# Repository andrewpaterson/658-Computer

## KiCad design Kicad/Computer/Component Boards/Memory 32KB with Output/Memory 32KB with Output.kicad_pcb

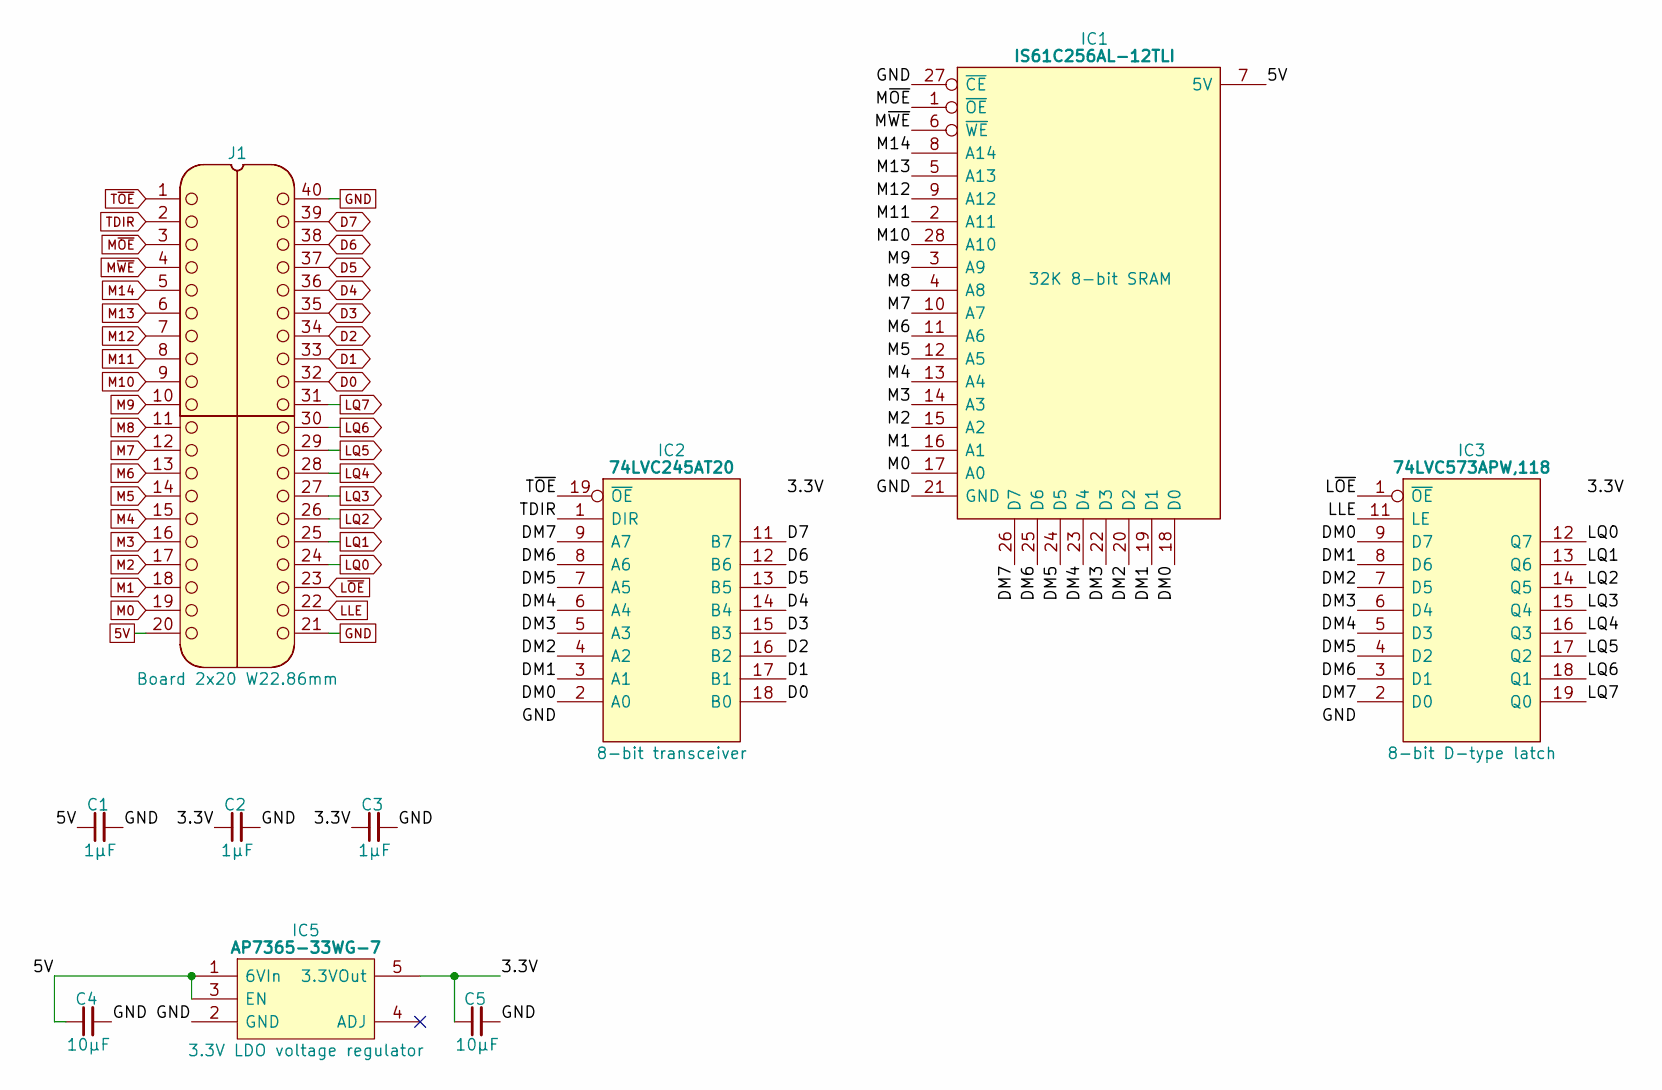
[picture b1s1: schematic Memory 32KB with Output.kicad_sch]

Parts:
C1, C2, C3: 1μF; C_0805
C4, C5: 10µF; C_0805
IC1: IS61C256AL-12TLI; SOP55P1340X120-28N; Manufacturer_Part_Number IS61C256AL-12TLI; Mouser Part Number 870-IS61C256AL-12TLI
IC2: 74LVC245AT20; SOP65P640X120-20N; Manufacturer_Part_Number 74LVC245AT20-13; Mouser Part Number 621-74LVC245AT20-13
IC3: 74LVC573APW,118; SOP65P640X110-20N; Mouser Part Number 771-74LVC573APW-T
IC5: AP7365-33WG-7; SOT95P285X130-5N; Manufacturer_Part_Number AP7365-33WG-7; Mouser Part Number 621-AP7365-33WG-7
J1: Board 2x20 W22.86mm; DIP-40_Board_W15.24mm_Alt

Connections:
5V: C1.1, C4.1, IC1.7 (5V), IC5.1 (6VIn), IC5.3 (EN), J1.20
/3.3V: C2.1, C3.1, C5.1, IC2.20 (3V), IC3.20 (3V), IC5.5 (3.3VOut)
/DM0: IC1.18 (D0), IC2.2 (A0), IC3.9 (D7)
/DM1: IC1.19 (D1), IC2.3 (A1), IC3.8 (D6)
/DM2: IC1.20 (D2), IC2.4 (A2), IC3.7 (D5)
/DM3: IC1.22 (D3), IC2.5 (A3), IC3.6 (D4)
/DM4: IC1.23 (D4), IC2.6 (A4), IC3.5 (D3)
/DM5: IC1.24 (D5), IC2.7 (A5), IC3.4 (D2)
/DM6: IC1.25 (D6), IC2.8 (A6), IC3.3 (D1)
/DM7: IC1.26 (D7), IC2.9 (A7), IC3.2 (D0)
D0: IC2.18 (B0), J1.32
D1: IC2.17 (B1), J1.33
D2: IC2.16 (B2), J1.34
D3: IC2.15 (B3), J1.35
D4: IC2.14 (B4), J1.36
D5: IC2.13 (B5), J1.37
D6: IC2.12 (B6), J1.38
D7: IC2.11 (B7), J1.39
GND: C1.2, C2.2, C3.2, C4.2, C5.2, IC1.21 (GND), IC1.27 (~CE), IC2.10 (GND), IC3.10 (GND), IC5.2 (GND), J1.21, J1.40
LLE: IC3.11 (LE), J1.22
LQ0: IC3.12 (Q7), J1.24
LQ1: IC3.13 (Q6), J1.25
LQ2: IC3.14 (Q5), J1.26
LQ3: IC3.15 (Q4), J1.27
LQ4: IC3.16 (Q3), J1.28
LQ5: IC3.17 (Q2), J1.29
LQ6: IC3.18 (Q1), J1.30
LQ7: IC3.19 (Q0), J1.31
L~OE: IC3.1 (~OE), J1.23
M0: IC1.17 (A0), J1.19
M1: IC1.16 (A1), J1.18
M2: IC1.15 (A2), J1.17
M3: IC1.14 (A3), J1.16
M4: IC1.13 (A4), J1.15
M5: IC1.12 (A5), J1.14
M6: IC1.11 (A6), J1.13
M7: IC1.10 (A7), J1.12
M8: IC1.4 (A8), J1.11
M9: IC1.3 (A9), J1.10
M10: IC1.28 (A10), J1.9
M11: IC1.2 (A11), J1.8
M12: IC1.9 (A12), J1.7
M13: IC1.5 (A13), J1.6
M14: IC1.8 (A14), J1.5
M~OE: IC1.1 (~OE), J1.3
M~WE: IC1.6 (~WE), J1.4
TDIR: IC2.1 (DIR), J1.2
T~OE: IC2.19 (~OE), J1.1

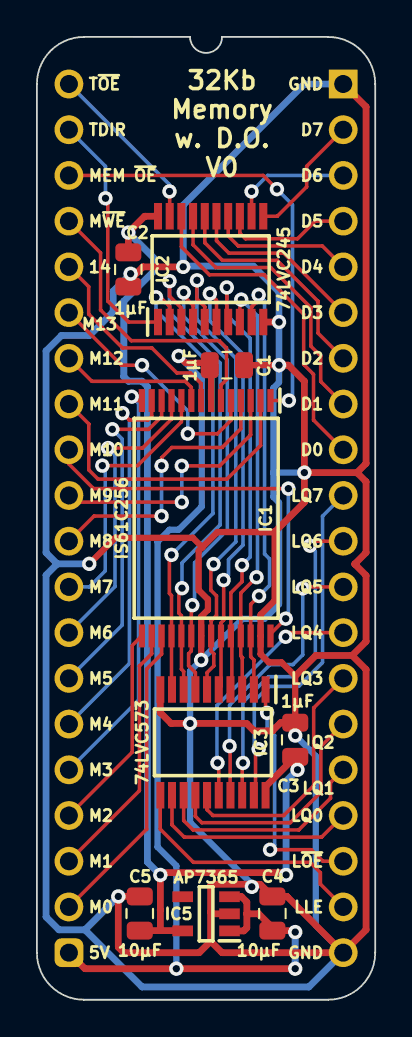
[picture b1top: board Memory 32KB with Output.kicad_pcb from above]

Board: 2 copper layers, 18.8 x 53.5 mm, 10 parts (0 on the bottom side), 48 nets.

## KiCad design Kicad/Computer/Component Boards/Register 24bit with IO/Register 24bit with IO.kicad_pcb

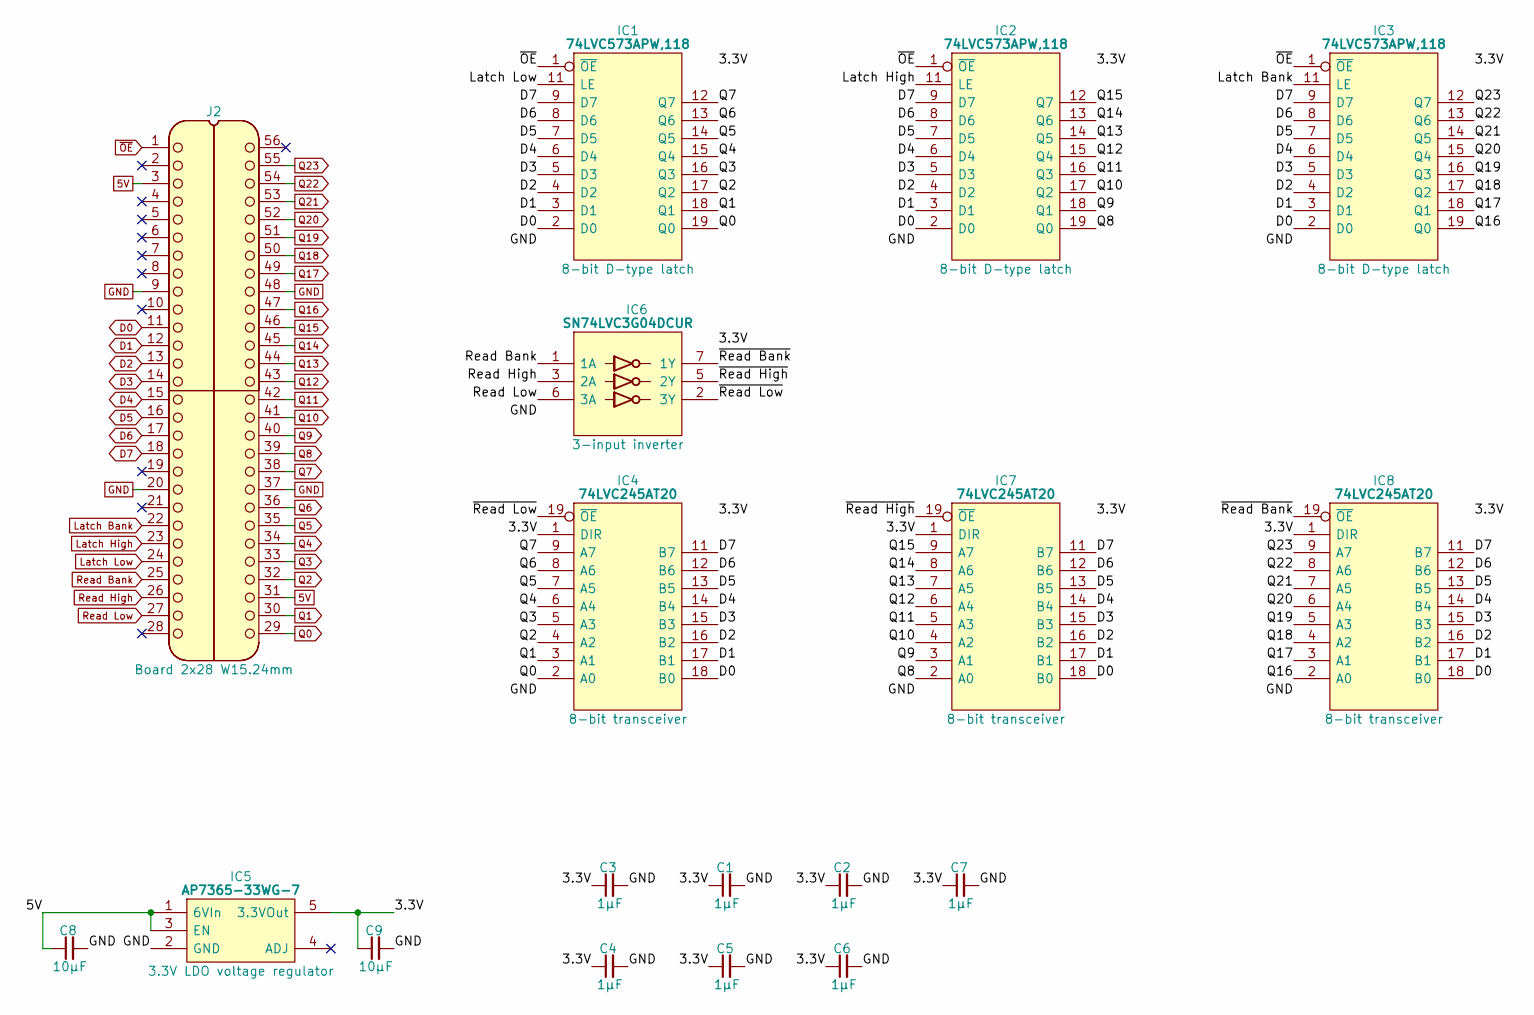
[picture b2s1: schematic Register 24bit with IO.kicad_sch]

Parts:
C1, C2, C3, C4, C5, C6, C7: 1μF; C_0805
C8, C9: 10µF; C_0805
IC1, IC2, IC3: 74LVC573APW,118; SOP65P640X110-20N; Manufacturer_Part_Number 74LVC573APW,118; Mouser Part Number 771-74LVC573APW-T
IC4, IC7, IC8: 74LVC245AT20; SOP65P640X120-20N; Manufacturer_Part_Number 74LVC245AT20-13; Mouser Part Number 621-74LVC245AT20-13
IC5: AP7365-33WG-7; SOT95P285X130-5N; Manufacturer_Part_Number AP7365-33WG-7; Mouser Part Number 621-AP7365-33WG-7
IC6: SN74LVC3G04DCUR; SOP50P310X90-8N; Manufacturer_Part_Number SN74LVC3G04DCUR; Mouser Part Number 595-SN74LVC3G04DCUR
J2: Board 2x28 W15.24mm; DIP-56_Board_W15.24mm

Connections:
5V: C8.1, IC5.1 (6VIn), IC5.3 (EN), J2.3, J2.31
/3.3V: C1.1, C2.1, C3.1, C4.1, C5.1, C6.1, C7.1, C9.1, IC1.20 (3V), IC2.20 (3V), IC3.20 (3V), IC4.1 (DIR), IC4.20 (3V), IC5.5 (3.3VOut), IC6.8 (3V), IC7.1 (DIR), IC7.20 (3V), IC8.1 (DIR), IC8.20 (3V)
/~Read Bank: IC6.7 (1Y), IC8.19 (~OE)
/~Read High: IC6.5 (2Y), IC7.19 (~OE)
/~Read Low: IC4.19 (~OE), IC6.2 (3Y)
D0: IC1.2 (D0), IC2.2 (D0), IC3.2 (D0), IC4.18 (B0), IC7.18 (B0), IC8.18 (B0), J2.11
D1: IC1.3 (D1), IC2.3 (D1), IC3.3 (D1), IC4.17 (B1), IC7.17 (B1), IC8.17 (B1), J2.12
D2: IC1.4 (D2), IC2.4 (D2), IC3.4 (D2), IC4.16 (B2), IC7.16 (B2), IC8.16 (B2), J2.13
D3: IC1.5 (D3), IC2.5 (D3), IC3.5 (D3), IC4.15 (B3), IC7.15 (B3), IC8.15 (B3), J2.14
D4: IC1.6 (D4), IC2.6 (D4), IC3.6 (D4), IC4.14 (B4), IC7.14 (B4), IC8.14 (B4), J2.15
D5: IC1.7 (D5), IC2.7 (D5), IC3.7 (D5), IC4.13 (B5), IC7.13 (B5), IC8.13 (B5), J2.16
D6: IC1.8 (D6), IC2.8 (D6), IC3.8 (D6), IC4.12 (B6), IC7.12 (B6), IC8.12 (B6), J2.17
D7: IC1.9 (D7), IC2.9 (D7), IC3.9 (D7), IC4.11 (B7), IC7.11 (B7), IC8.11 (B7), J2.18
GND: C1.2, C2.2, C3.2, C4.2, C5.2, C6.2, C7.2, C8.2, C9.2, IC1.10 (GND), IC2.10 (GND), IC3.10 (GND), IC4.10 (GND), IC5.2 (GND), IC6.4 (GND), IC7.10 (GND), IC8.10 (GND), J2.9, J2.20, J2.37, J2.48
Latch Bank: IC3.11 (LE), J2.22
Latch High: IC2.11 (LE), J2.23
Latch Low: IC1.11 (LE), J2.24
Q0: IC1.19 (Q0), IC4.2 (A0), J2.29
Q1: IC1.18 (Q1), IC4.3 (A1), J2.30
Q2: IC1.17 (Q2), IC4.4 (A2), J2.32
Q3: IC1.16 (Q3), IC4.5 (A3), J2.33
Q4: IC1.15 (Q4), IC4.6 (A4), J2.34
Q5: IC1.14 (Q5), IC4.7 (A5), J2.35
Q6: IC1.13 (Q6), IC4.8 (A6), J2.36
Q7: IC1.12 (Q7), IC4.9 (A7), J2.38
Q8: IC2.19 (Q0), IC7.2 (A0), J2.39
Q9: IC2.18 (Q1), IC7.3 (A1), J2.40
Q10: IC2.17 (Q2), IC7.4 (A2), J2.41
Q11: IC2.16 (Q3), IC7.5 (A3), J2.42
Q12: IC2.15 (Q4), IC7.6 (A4), J2.43
Q13: IC2.14 (Q5), IC7.7 (A5), J2.44
Q14: IC2.13 (Q6), IC7.8 (A6), J2.45
Q15: IC2.12 (Q7), IC7.9 (A7), J2.46
Q16: IC3.19 (Q0), IC8.2 (A0), J2.47
Q17: IC3.18 (Q1), IC8.3 (A1), J2.49
Q18: IC3.17 (Q2), IC8.4 (A2), J2.50
Q19: IC3.16 (Q3), IC8.5 (A3), J2.51
Q20: IC3.15 (Q4), IC8.6 (A4), J2.52
Q21: IC3.14 (Q5), IC8.7 (A5), J2.53
Q22: IC3.13 (Q6), IC8.8 (A6), J2.54
Q23: IC3.12 (Q7), IC8.9 (A7), J2.55
Read Bank: IC6.1 (1A), J2.25
Read High: IC6.3 (2A), J2.26
Read Low: IC6.6 (3A), J2.27
~OE: IC1.1 (~OE), IC2.1 (~OE), IC3.1 (~OE), J2.1

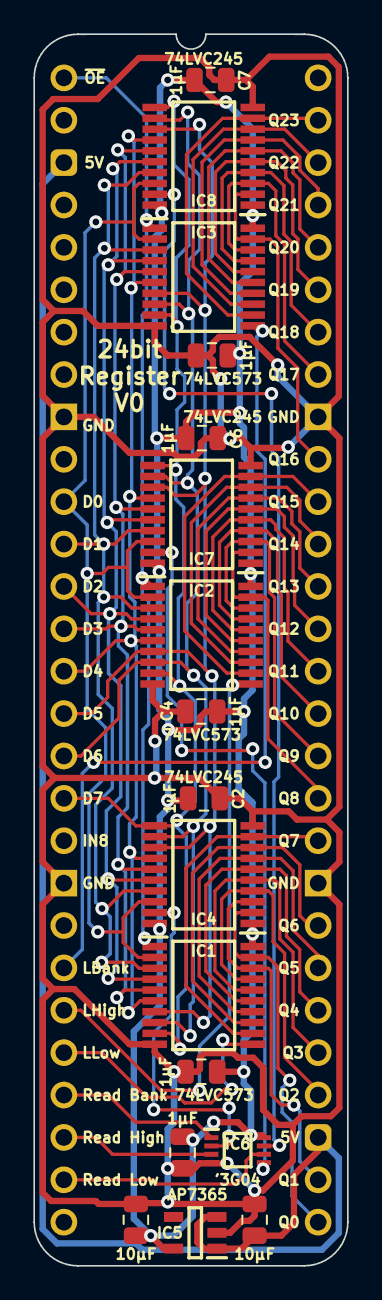
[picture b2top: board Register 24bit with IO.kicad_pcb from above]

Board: 2 copper layers, 18.8 x 73.8 mm, 18 parts (0 on the bottom side), 45 nets.

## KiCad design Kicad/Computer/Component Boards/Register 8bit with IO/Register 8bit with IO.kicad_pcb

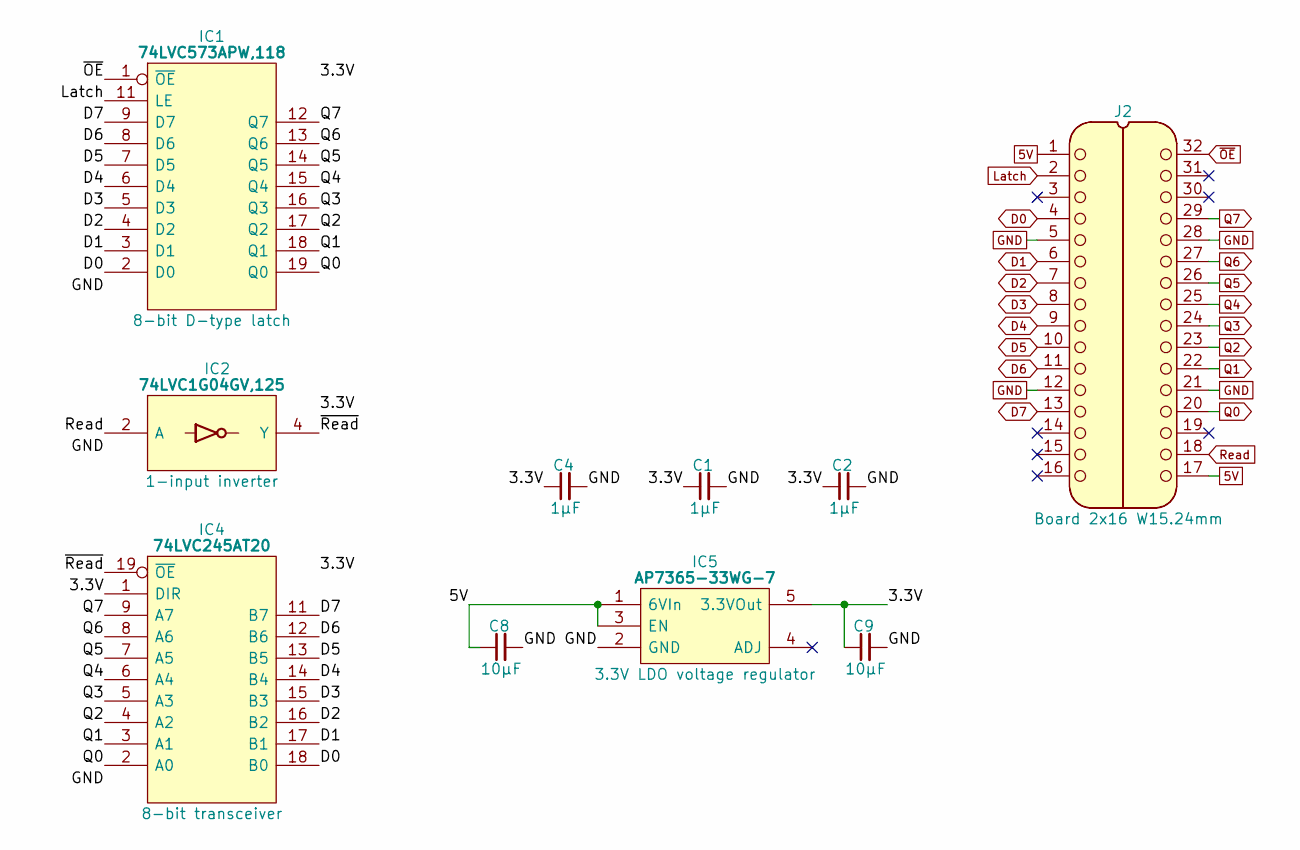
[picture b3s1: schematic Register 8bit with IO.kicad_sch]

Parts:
C1, C2, C4: 1μF; C_0805
C8, C9: 10µF; C_0805
IC1: 74LVC573APW,118; SOP65P640X110-20N; Manufacturer_Part_Number 74LVC573APW,118; Mouser Part Number 771-74LVC573APW-T
IC2: 74LVC1G04GV,125; SOT95P275X110-5N; Manufacturer_Part_Number 74LVC1G04GV,125; Mouser Part Number 771-74LVC1G04GV
IC4: 74LVC245AT20; SOP65P640X120-20N; Manufacturer_Part_Number 74LVC245AT20-13; Mouser Part Number 621-74LVC245AT20-13
IC5: AP7365-33WG-7; SOT95P285X130-5N; Manufacturer_Part_Number AP7365-33WG-7; Mouser Part Number 621-AP7365-33WG-7
J2: Board 2x16 W15.24mm; DIP-32_Board_W15.24mm

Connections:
5V: C8.1, IC5.1 (6VIn), IC5.3 (EN), J2.1, J2.17
/3.3V: C1.1, C2.1, C4.1, C9.1, IC1.20 (3V), IC2.5 (3V), IC4.1 (DIR), IC4.20 (3V), IC5.5 (3.3VOut)
/~Read: IC2.4 (Y), IC4.19 (~OE)
D0: IC1.2 (D0), IC4.18 (B0), J2.4
D1: IC1.3 (D1), IC4.17 (B1), J2.6
D2: IC1.4 (D2), IC4.16 (B2), J2.7
D3: IC1.5 (D3), IC4.15 (B3), J2.8
D4: IC1.6 (D4), IC4.14 (B4), J2.9
D5: IC1.7 (D5), IC4.13 (B5), J2.10
D6: IC1.8 (D6), IC4.12 (B6), J2.11
D7: IC1.9 (D7), IC4.11 (B7), J2.13
GND: C1.2, C2.2, C4.2, C8.2, C9.2, IC1.10 (GND), IC2.3 (GND), IC4.10 (GND), IC5.2 (GND), J2.5, J2.12, J2.21, J2.28
Latch: IC1.11 (LE), J2.2
Q0: IC1.19 (Q0), IC4.2 (A0), J2.20
Q1: IC1.18 (Q1), IC4.3 (A1), J2.22
Q2: IC1.17 (Q2), IC4.4 (A2), J2.23
Q3: IC1.16 (Q3), IC4.5 (A3), J2.24
Q4: IC1.15 (Q4), IC4.6 (A4), J2.25
Q5: IC1.14 (Q5), IC4.7 (A5), J2.26
Q6: IC1.13 (Q6), IC4.8 (A6), J2.27
Q7: IC1.12 (Q7), IC4.9 (A7), J2.29
Read: IC2.2 (A), J2.18
~OE: IC1.1 (~OE), J2.32

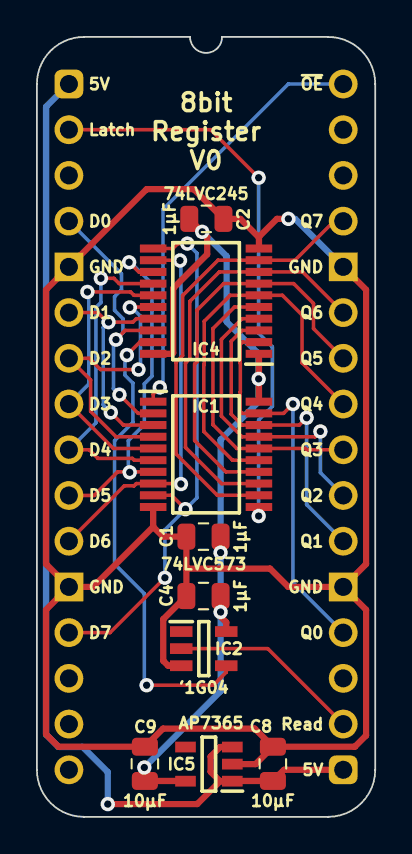
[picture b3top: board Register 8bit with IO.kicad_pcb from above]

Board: 2 copper layers, 18.8 x 43.3 mm, 10 parts (0 on the bottom side), 23 nets.

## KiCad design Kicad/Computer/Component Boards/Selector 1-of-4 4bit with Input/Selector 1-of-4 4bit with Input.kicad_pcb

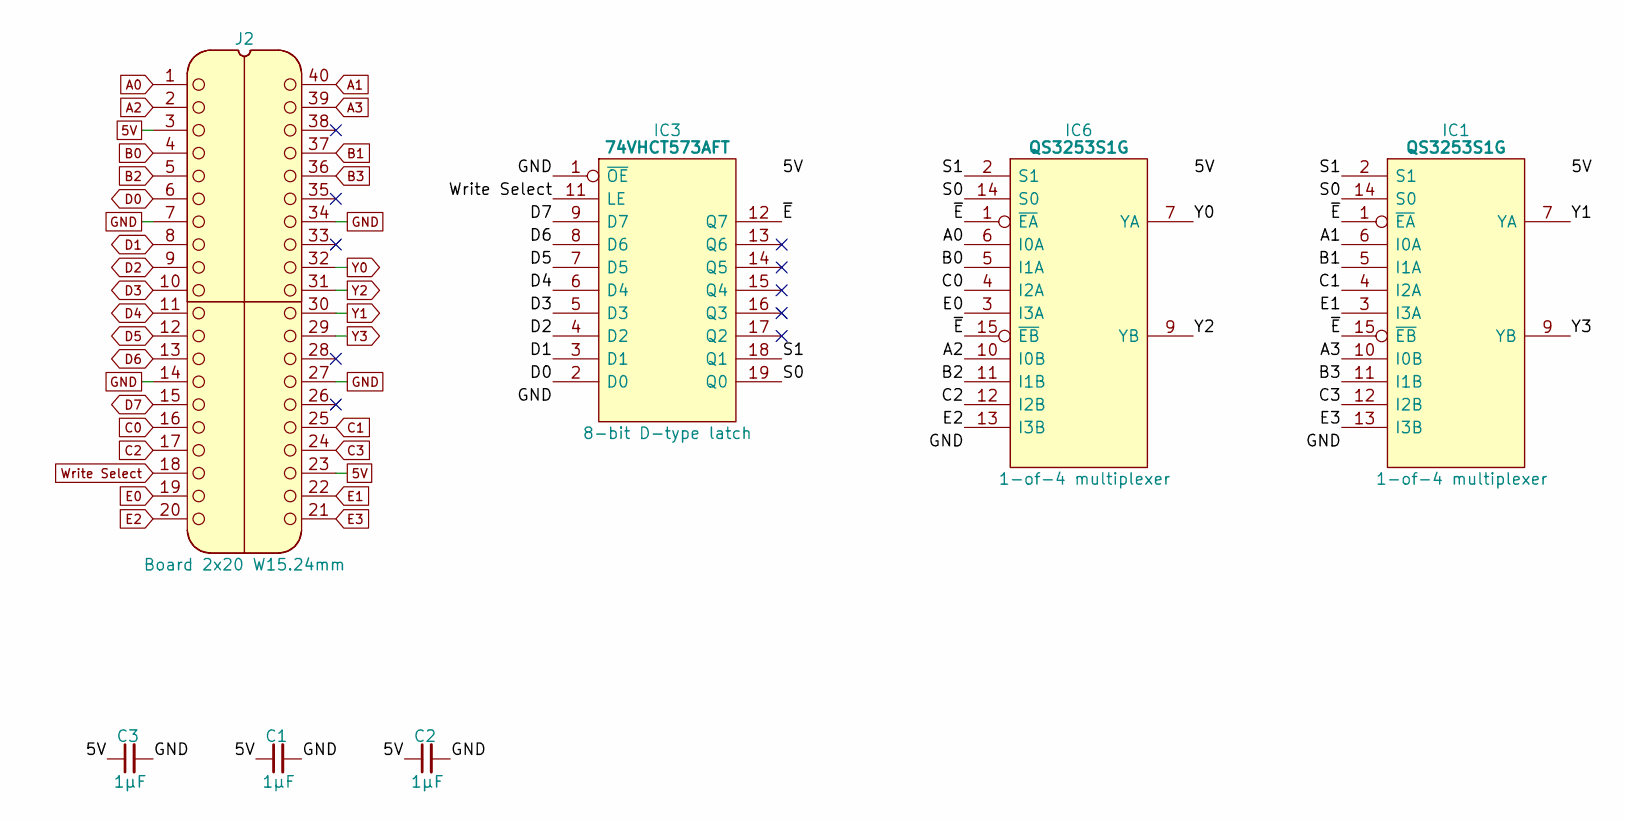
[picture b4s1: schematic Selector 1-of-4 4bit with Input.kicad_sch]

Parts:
C1, C2, C3: 1μF; C_0805
IC1, IC6: QS3253S1G; SOIC127P602X173-16N; Manufacturer_Part_Number QS3253S1G
IC3: 74VHCT573AFT; SOP65P640X120-20N; Manufacturer_Part_Number 74VHCT573AFT; Mouser Part Number N/A
J2: Board 2x20 W15.24mm; DIP-40_Board_W15.24mm

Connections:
5V: C1.1, C2.1, C3.1, IC1.16 (5V), IC3.20 (5V), IC6.16 (5V), J2.3, J2.23
/S0: IC1.14 (S0), IC3.19 (Q0), IC6.14 (S0)
/S1: IC1.2 (S1), IC3.18 (Q1), IC6.2 (S1)
/~E: IC1.1 (~EA), IC1.15 (~EB), IC3.12 (Q7), IC6.1 (~EA), IC6.15 (~EB)
A0: IC6.6 (I0A), J2.1
A1: IC1.6 (I0A), J2.40
A2: IC6.10 (I0B), J2.2
A3: IC1.10 (I0B), J2.39
B0: IC6.5 (I1A), J2.4
B1: IC1.5 (I1A), J2.37
B2: IC6.11 (I1B), J2.5
B3: IC1.11 (I1B), J2.36
C0: IC6.4 (I2A), J2.16
C1: IC1.4 (I2A), J2.25
C2: IC6.12 (I2B), J2.17
C3: IC1.12 (I2B), J2.24
D0: IC3.2 (D0), J2.6
D1: IC3.3 (D1), J2.8
D2: IC3.4 (D2), J2.9
D3: IC3.5 (D3), J2.10
D4: IC3.6 (D4), J2.11
D5: IC3.7 (D5), J2.12
D6: IC3.8 (D6), J2.13
D7: IC3.9 (D7), J2.15
E0: IC6.3 (I3A), J2.19
E1: IC1.3 (I3A), J2.22
E2: IC6.13 (I3B), J2.20
E3: IC1.13 (I3B), J2.21
GND: C1.2, C2.2, C3.2, IC1.8 (GND), IC3.1 (~OE), IC3.10 (GND), IC6.8 (GND), J2.7, J2.14, J2.27, J2.34
Write Select: IC3.11 (LE), J2.18
Y0: IC6.7 (YA), J2.32
Y1: IC1.7 (YA), J2.30
Y2: IC6.9 (YB), J2.31
Y3: IC1.9 (YB), J2.29

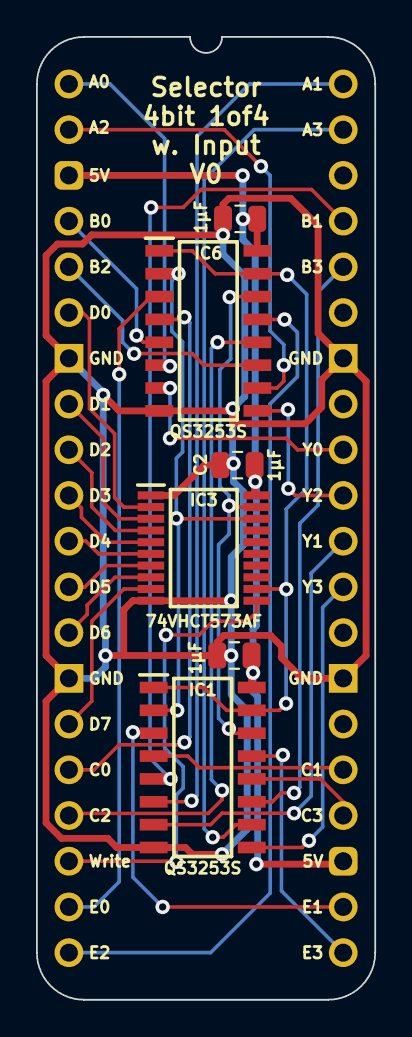
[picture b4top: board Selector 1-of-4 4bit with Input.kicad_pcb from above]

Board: 2 copper layers, 18.8 x 53.5 mm, 7 parts (0 on the bottom side), 34 nets.

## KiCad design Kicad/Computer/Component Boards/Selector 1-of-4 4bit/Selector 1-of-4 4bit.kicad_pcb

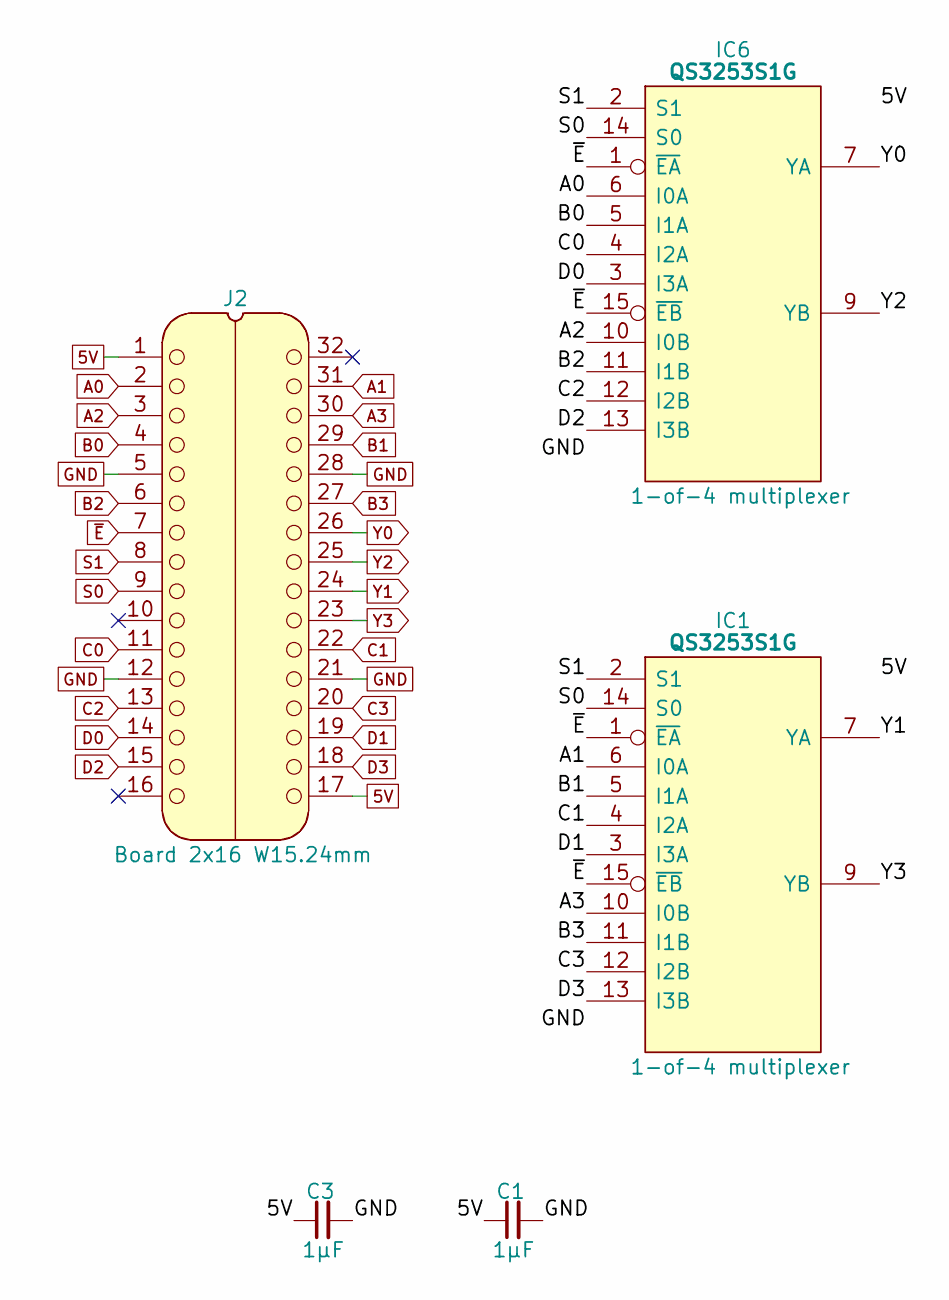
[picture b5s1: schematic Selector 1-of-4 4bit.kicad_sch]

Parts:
C1, C3: 1μF; C_0805
IC1, IC6: QS3253S1G; SOIC127P602X173-16N; Manufacturer_Part_Number QS3253S1G
J2: Board 2x16 W15.24mm; DIP-32_Board_W15.24mm

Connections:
5V: C1.1, C3.1, IC1.16 (5V), IC6.16 (5V), J2.1, J2.17
A0: IC6.6 (I0A), J2.2
A1: IC1.6 (I0A), J2.31
A2: IC6.10 (I0B), J2.3
A3: IC1.10 (I0B), J2.30
B0: IC6.5 (I1A), J2.4
B1: IC1.5 (I1A), J2.29
B2: IC6.11 (I1B), J2.6
B3: IC1.11 (I1B), J2.27
C0: IC6.4 (I2A), J2.11
C1: IC1.4 (I2A), J2.22
C2: IC6.12 (I2B), J2.13
C3: IC1.12 (I2B), J2.20
D0: IC6.3 (I3A), J2.14
D1: IC1.3 (I3A), J2.19
D2: IC6.13 (I3B), J2.15
D3: IC1.13 (I3B), J2.18
GND: C1.2, C3.2, IC1.8 (GND), IC6.8 (GND), J2.5, J2.12, J2.21, J2.28
S0: IC1.14 (S0), IC6.14 (S0), J2.9
S1: IC1.2 (S1), IC6.2 (S1), J2.8
Y0: IC6.7 (YA), J2.26
Y1: IC1.7 (YA), J2.24
Y2: IC6.9 (YB), J2.25
Y3: IC1.9 (YB), J2.23
~E: IC1.1 (~EA), IC1.15 (~EB), IC6.1 (~EA), IC6.15 (~EB), J2.7

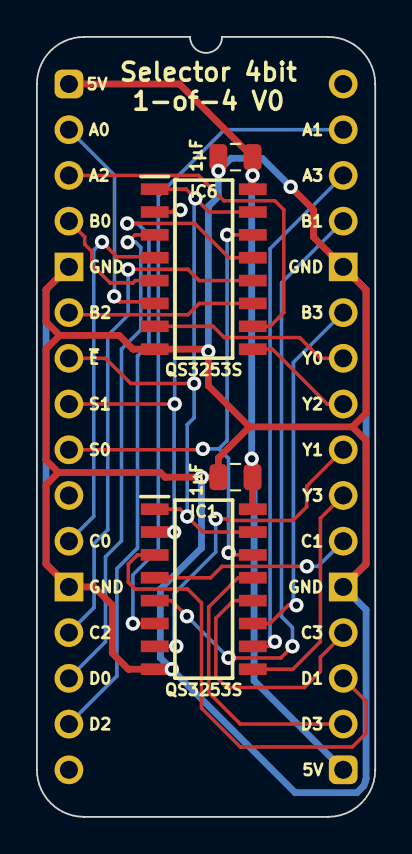
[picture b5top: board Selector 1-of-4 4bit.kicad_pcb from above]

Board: 2 copper layers, 18.8 x 43.3 mm, 5 parts (0 on the bottom side), 25 nets.

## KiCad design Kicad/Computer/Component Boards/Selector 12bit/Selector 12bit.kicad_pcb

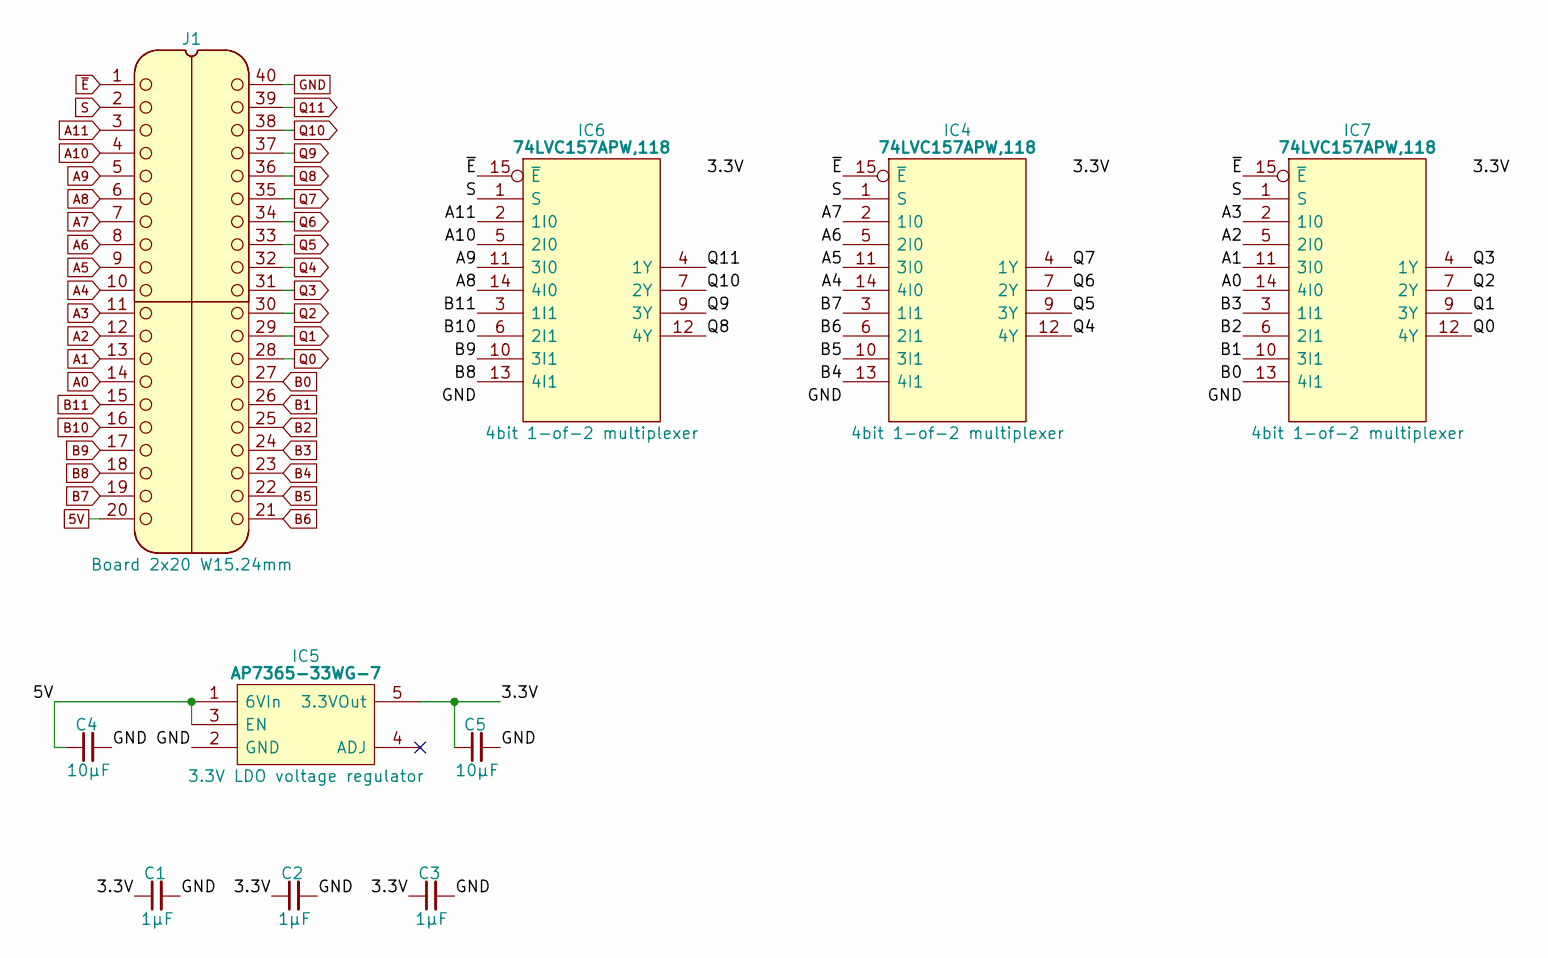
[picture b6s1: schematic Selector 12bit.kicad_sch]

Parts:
C1, C2, C3: 1μF; C_0805
C4, C5: 10µF; C_0805
IC4, IC6, IC7: 74LVC157APW,118; SOP65P640X110-16N; Mouser Part Number 771-74LVC157APW-T
IC5: AP7365-33WG-7; SOT95P285X130-5N; Manufacturer_Part_Number AP7365-33WG-7; Mouser Part Number 621-AP7365-33WG-7
J1: Board 2x20 W15.24mm; DIP-40_Board_W15.24mm_Alt

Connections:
5V: C4.1, IC5.1 (6VIn), IC5.3 (EN), J1.20
/3.3V: C1.1, C2.1, C3.1, C5.1, IC4.16 (3V), IC5.5 (3.3VOut), IC6.16 (3V), IC7.16 (3V)
A0: IC7.14 (4I0), J1.14
A1: IC7.11 (3I0), J1.13
A2: IC7.5 (2I0), J1.12
A3: IC7.2 (1I0), J1.11
A4: IC4.14 (4I0), J1.10
A5: IC4.11 (3I0), J1.9
A6: IC4.5 (2I0), J1.8
A7: IC4.2 (1I0), J1.7
A8: IC6.14 (4I0), J1.6
A9: IC6.11 (3I0), J1.5
A10: IC6.5 (2I0), J1.4
A11: IC6.2 (1I0), J1.3
B0: IC7.13 (4I1), J1.27
B1: IC7.10 (3I1), J1.26
B2: IC7.6 (2I1), J1.25
B3: IC7.3 (1I1), J1.24
B4: IC4.13 (4I1), J1.23
B5: IC4.10 (3I1), J1.22
B6: IC4.6 (2I1), J1.21
B7: IC4.3 (1I1), J1.19
B8: IC6.13 (4I1), J1.18
B9: IC6.10 (3I1), J1.17
B10: IC6.6 (2I1), J1.16
B11: IC6.3 (1I1), J1.15
GND: C1.2, C2.2, C3.2, C4.2, C5.2, IC4.8 (GND), IC5.2 (GND), IC6.8 (GND), IC7.8 (GND), J1.40
Q0: IC7.12 (4Y), J1.28
Q1: IC7.9 (3Y), J1.29
Q2: IC7.7 (2Y), J1.30
Q3: IC7.4 (1Y), J1.31
Q4: IC4.12 (4Y), J1.32
Q5: IC4.9 (3Y), J1.33
Q6: IC4.7 (2Y), J1.34
Q7: IC4.4 (1Y), J1.35
Q8: IC6.12 (4Y), J1.36
Q9: IC6.9 (3Y), J1.37
Q10: IC6.7 (2Y), J1.38
Q11: IC6.4 (1Y), J1.39
S: IC4.1 (S), IC6.1 (S), IC7.1 (S), J1.2
~E: IC4.15 (~E), IC6.15 (~E), IC7.15 (~E), J1.1

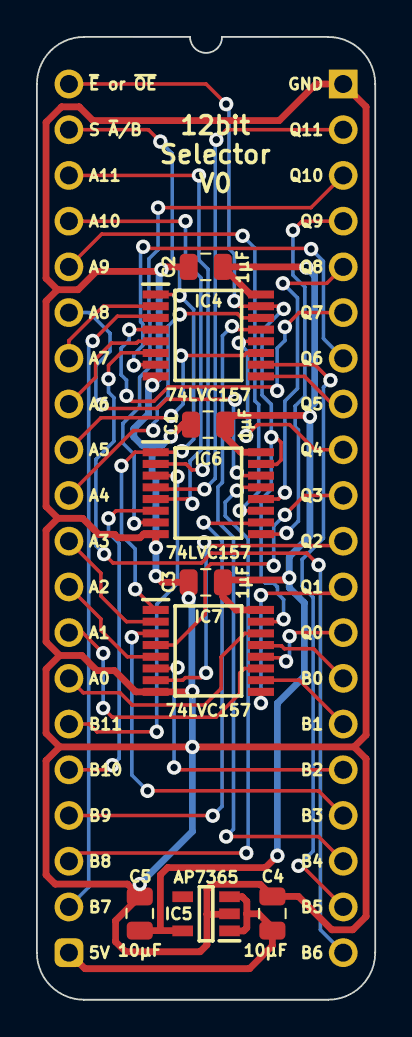
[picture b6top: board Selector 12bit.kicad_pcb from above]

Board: 2 copper layers, 18.8 x 53.5 mm, 10 parts (0 on the bottom side), 41 nets.

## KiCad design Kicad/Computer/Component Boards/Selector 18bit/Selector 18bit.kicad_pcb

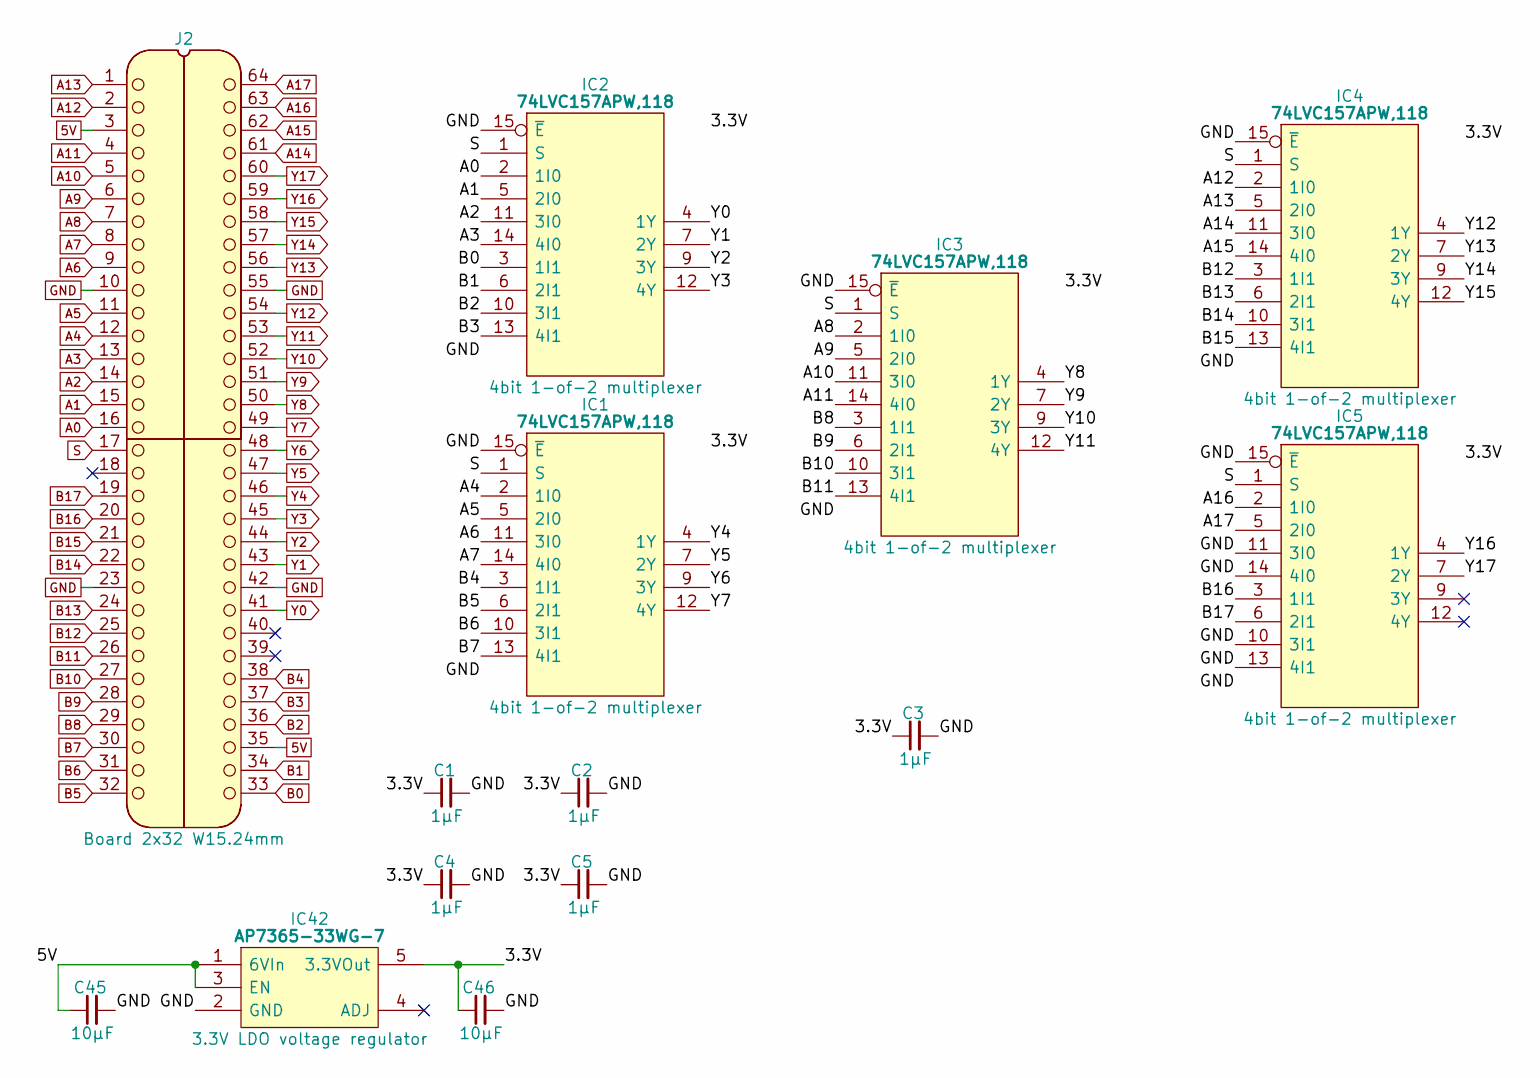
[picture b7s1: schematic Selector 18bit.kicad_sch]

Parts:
C1, C2, C3, C4, C5: 1μF; C_0805
C45, C46: 10μF; C_0805
IC1, IC2, IC3, IC4, IC5: 74LVC157APW,118; SOP65P640X110-16N; Mouser Part Number 771-74LVC157APW-T
IC42: AP7365-33WG-7; SOT95P285X130-5N; Manufacturer_Part_Number AP7365-33WG-7; Mouser Part Number 621-AP7365-33WG-7
J2: Board 2x32 W15.24mm; DIP-64_Board_W15.24mm

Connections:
5V: C45.1, IC42.1 (6VIn), IC42.3 (EN), J2.3, J2.35
/3.3V: C1.1, C2.1, C3.1, C4.1, C5.1, C46.1, IC1.16 (3V), IC2.16 (3V), IC3.16 (3V), IC4.16 (3V), IC5.16 (3V), IC42.5 (3.3VOut)
A0: IC2.2 (1I0), J2.16
A1: IC2.5 (2I0), J2.15
A2: IC2.11 (3I0), J2.14
A3: IC2.14 (4I0), J2.13
A4: IC1.2 (1I0), J2.12
A5: IC1.5 (2I0), J2.11
A6: IC1.11 (3I0), J2.9
A7: IC1.14 (4I0), J2.8
A8: IC3.2 (1I0), J2.7
A9: IC3.5 (2I0), J2.6
A10: IC3.11 (3I0), J2.5
A11: IC3.14 (4I0), J2.4
A12: IC4.2 (1I0), J2.2
A13: IC4.5 (2I0), J2.1
A14: IC4.11 (3I0), J2.61
A15: IC4.14 (4I0), J2.62
A16: IC5.2 (1I0), J2.63
A17: IC5.5 (2I0), J2.64
B0: IC2.3 (1I1), J2.33
B1: IC2.6 (2I1), J2.34
B2: IC2.10 (3I1), J2.36
B3: IC2.13 (4I1), J2.37
B4: IC1.3 (1I1), J2.38
B5: IC1.6 (2I1), J2.32
B6: IC1.10 (3I1), J2.31
B7: IC1.13 (4I1), J2.30
B8: IC3.3 (1I1), J2.29
B9: IC3.6 (2I1), J2.28
B10: IC3.10 (3I1), J2.27
B11: IC3.13 (4I1), J2.26
B12: IC4.3 (1I1), J2.25
B13: IC4.6 (2I1), J2.24
B14: IC4.10 (3I1), J2.22
B15: IC4.13 (4I1), J2.21
B16: IC5.3 (1I1), J2.20
B17: IC5.6 (2I1), J2.19
GND: C1.2, C2.2, C3.2, C4.2, C5.2, C45.2, C46.2, IC1.8 (GND), IC1.15 (~E), IC2.8 (GND), IC2.15 (~E), IC3.8 (GND), IC3.15 (~E), IC4.8 (GND), IC4.15 (~E), IC5.8 (GND), IC5.10 (3I1), IC5.11 (3I0), IC5.13 (4I1), IC5.14 (4I0), IC5.15 (~E), IC42.2 (GND), J2.10, J2.23, J2.42, J2.55
S: IC1.1 (S), IC2.1 (S), IC3.1 (S), IC4.1 (S), IC5.1 (S), J2.17
Y0: IC2.4 (1Y), J2.41
Y1: IC2.7 (2Y), J2.43
Y2: IC2.9 (3Y), J2.44
Y3: IC2.12 (4Y), J2.45
Y4: IC1.4 (1Y), J2.46
Y5: IC1.7 (2Y), J2.47
Y6: IC1.9 (3Y), J2.48
Y7: IC1.12 (4Y), J2.49
Y8: IC3.4 (1Y), J2.50
Y9: IC3.7 (2Y), J2.51
Y10: IC3.9 (3Y), J2.52
Y11: IC3.12 (4Y), J2.53
Y12: IC4.4 (1Y), J2.54
Y13: IC4.7 (2Y), J2.56
Y14: IC4.9 (3Y), J2.57
Y15: IC4.12 (4Y), J2.58
Y16: IC5.4 (1Y), J2.59
Y17: IC5.7 (2Y), J2.60

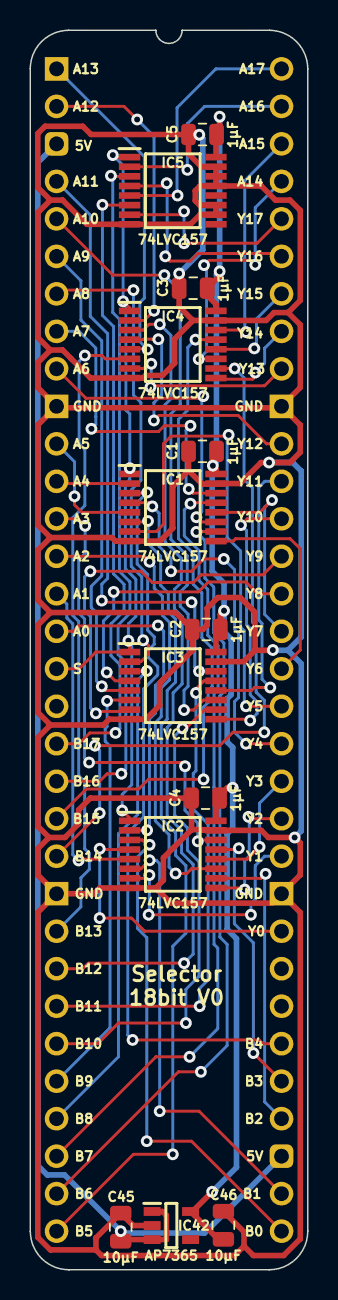
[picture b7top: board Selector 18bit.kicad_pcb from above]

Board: 2 copper layers, 18.8 x 84.0 mm, 14 parts (0 on the bottom side), 58 nets.
